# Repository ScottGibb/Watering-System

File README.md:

# Watering System

## System Diagram

Hardware for a watering system split across two boards, linked by a multicore
cable:

- **Main Board** contains the controller and main watering-system circuitry.
  Open [main-board/main-board.kicad_pro](main-board/main-board.kicad_pro).
- **Connector Board** breaks out the multicore cable to the external connections.
  Open [connector-board/connector-board.kicad_pro](connector-board/connector-board.kicad_pro).

Each folder contains a matching `.kicad_pro`, `.kicad_sch`, and `.kicad_pcb`.
Use KiCad 10 to open the projects. CI currently checks and releases schematics;
PCB checks and fabrication outputs are not enabled.

[Wiring harnesses](wiring/README.md) are maintained separately in `wiring/` using
WireViz, including confirmed pin mappings and explicitly unresolved physical details.

## Veroboards and Pictures

The populated main veroboard, ESP8266 controller and relay modules installed in
the electronics case:

## CAD files

CAD files and printable parts for the watering-system cases:

| Case | Thingiverse | Printables |
| --- | --- | --- |
| Veroboard Ribbon Enclosure | [Files](https://www.thingiverse.com/thing:7423750) | [Files](https://www.printables.com/model/1882002) |
| Plant Pot PIR Sensor Case | [Files](https://www.thingiverse.com/thing:7423472) | [Files](https://www.printables.com/model/1880769) |
| Plant Pot Electronics Case | [Files](https://www.thingiverse.com/thing:7423784) | [Files](https://www.printables.com/model/1882130) |

These listings were last recorded as drafts; links may be unavailable until
the models are published.

## External hardware

Component links and references for the build. Supplier examples are not a
complete BOM; check supply voltage, pinout and dimensions against the wiring
documentation and your actual parts.

- **Moisture sensors:** [capacitive soil moisture sensor](https://thepihut.com/products/capacitive-soil-moisture-sensor)
  for the outdoor probes; the indoor probe uses a resistive sensor.
- **Relays:** two HL-51 V1.0 single-channel modules
  ([module CAD reference](https://grabcad.com/library/relay-module-1-1)).
- **Water pumps:** two low-voltage DC pumps
  ([example submersible pump](https://thepihut.com/collections/maker-store/products/submersible-3v-dc-water-pump-vertical-type));
  the exact installed pump model is unconfirmed.
- **PIR sensor:** [AM312 mini PIR sensor](https://247geek.co.uk/am312).
- **ESP8266 controller:** [NodeMCU LoLin V3 board examples](https://www.az-delivery.uk/collections/nodemcu).

## KiCad libraries and drawing sheets

After cloning the repository, initialise the pinned library submodule:

```sh
git submodule update --init --recursive
```

Main Board registers the vendor ESP8266 symbol and footprint libraries as
`ESP8266` through its project-local `sym-lib-table` and `fp-lib-table`.
Both use `${KIPRJMOD}/../vendor/` paths, so no machine-specific library
configuration is required. Close and reopen the project if its editors were
already open when the library tables changed.

- Symbol library: `ESP8266` (legacy `.lib`, including `NodeMCU1.0(ESP-12E)`
  and `NodeMCU_1.0_(ESP-12E)`).
- LOLIN V3 footprint: `ESP8266:NodeMCU-LoLinV3`.

The vendor library has a LOLIN V3 footprint but no dedicated LOLIN V3 symbol.
Verify the symbol pin mapping against the actual board before assigning that
footprint; registering the libraries does not place or connect a module.

Main Board references the shared drawing sheet in
`templates/scott-gibb-template.kicad_wks` using a project-relative path.
Connector Board retains its embedded copy of the drawing sheet.

## Continuous integration

CI runs ERC for both boards and exports schematic PDFs, SVGs, BOMs, and netlists.
Artifacts are named per board and retained for seven days. MegaLinter checks
Markdown, YAML, JSON, and workflows.
WireViz builds harness diagrams and BOMs, with seven-day artifact retention.

## Independent board releases

Release Please manages separate versions, changelogs, release PRs, and GitHub
releases for each board. Tags use `main-board-v1.0.0` and
`connector-board-v1.0.0` formats. Both boards start at version `1.0.0`.

Use conventional commits such as `fix(main-board): correct sensor wiring`.
Changed file paths determine which board is released. After successful KiCad
checks, each release receives its own schematic exports and ERC report.
Wiring has an independent version and changelog with `wiring-v*` tags; its releases
receive a ZIP of harness YAML, diagrams and BOMs.

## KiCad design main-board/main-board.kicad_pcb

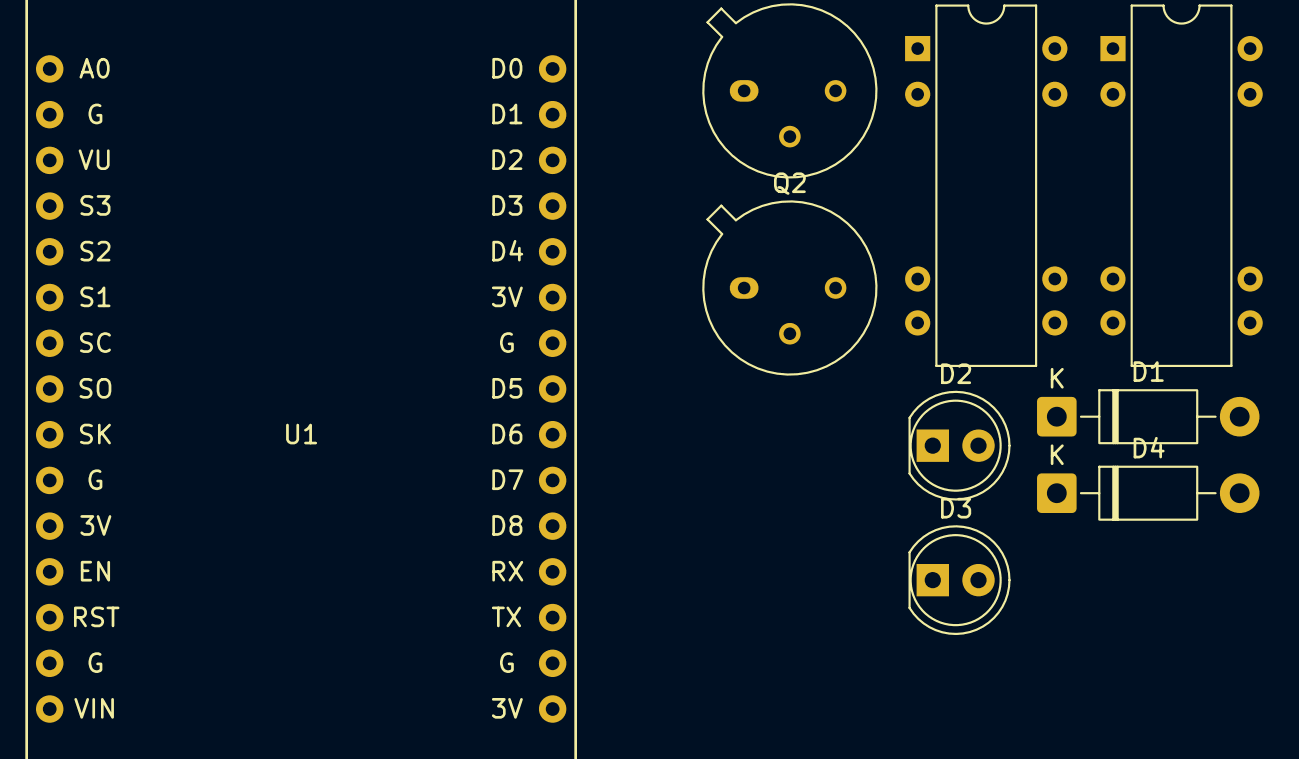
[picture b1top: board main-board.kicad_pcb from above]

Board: 2 copper layers, 9 parts (0 on the bottom side), 6 nets, no tracks yet.

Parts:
D1, D4: 1N4007; D_DO-41_SOD81_P10.16mm_Horizontal
D2, D3: LD271; LED_D5.0mm_IRGrey
K2, K3: DIPxx-1Cxx-51x; Relay_StandexMeder_DIP_LowProfile
Q1, Q2: 2N2219; TO-39-3
U1: NodeMCU_1.0_(ESP-12E); NodeMCU-LoLinV3

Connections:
+3V3: U1.11 (3.3V), U1.16 (3.3V), U1.25 (3.3V)
+5V: D1.1 (K), D4.1 (K), K2.6, K3.6, U1.15 (VIN)
GND: Q1.1 (E), Q2.1 (E), U1.10 (GND), U1.14 (GND), U1.17 (GND), U1.24 (GND)
unnamed: D1.2 (A), D2.1 (K), K2.2, Q1.3 (C)
unnamed: D3.1 (K), D4.2 (A), K3.2, Q2.3 (C)
VCC: K2.7, K2.8, K3.7, K3.8
